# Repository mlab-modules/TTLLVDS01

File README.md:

<!--- PrjInfo ---> <!--- Please remove this line after manually editing --->
<!--- 00a56be08b96043df9e37d6aff7b6990 --->
<!--- Created:2019-02-18 14:57:49.031132: ---> 
<!--- Author:: ---> 
<!--- AuthorEmail:: ---> 
<!--- Tags:: ---> 
<!--- Ust:: ---> 
<!--- Label --->
<!--- ELabel ---> 
<!--- Name:TTLLVDS01A: --->
# TTLLVDS01A
<!--- LongName --->
## TTL to LVDS converter and vice versa
<!--- ELongName ---> 

<!--- Lead --->
TTLLVDS is TTL to LVDS and LVDS to TTL converter. Module can be used to connect a simple TTL signal to LVDS input. By changing the components, it can acts as LVDS to TTL convertor. To covert differencial LVDS signal to TTL output. Each module converts two signals. 
<!--- ELead ---> 

<!--- Description --->
The TTL signal is connected using a simple header. Differential LVDS signal is connected trought SATA connector and cable. Each sata connector contains two pairs of LVDS signals.

Module require a 3v3 powering. 
<!--- EDescription --->
<!--- Content --->
<!--- EContent --->

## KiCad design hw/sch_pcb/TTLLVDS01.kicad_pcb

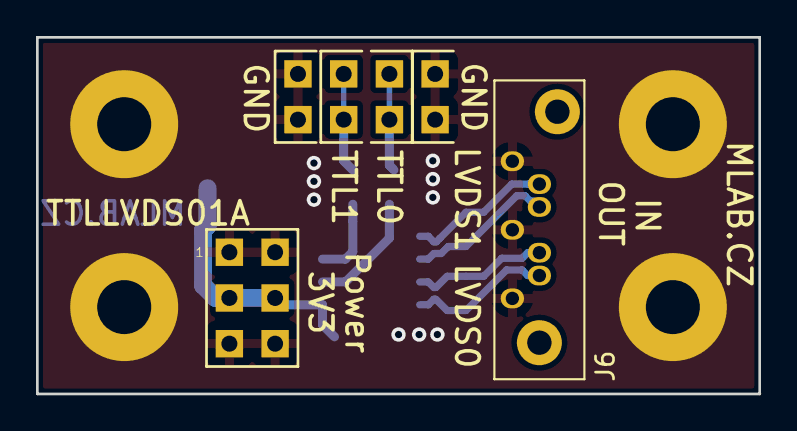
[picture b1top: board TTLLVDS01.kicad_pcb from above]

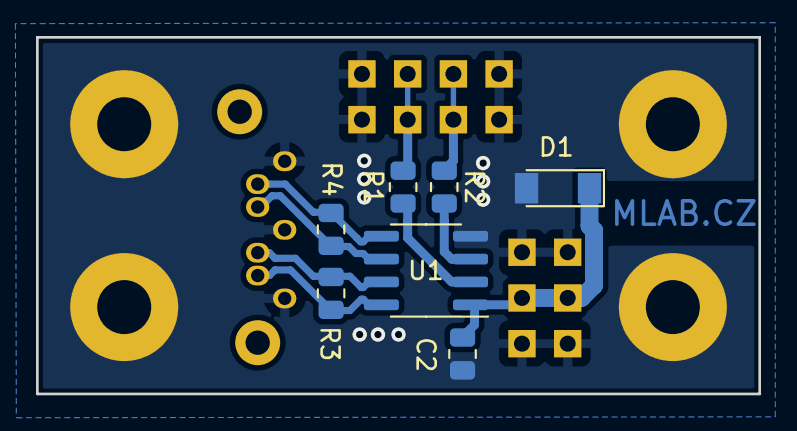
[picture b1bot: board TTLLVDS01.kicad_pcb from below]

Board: 2 copper layers, 40.1 x 19.8 mm, 17 parts (7 on the bottom side), 10 nets.

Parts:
C2: 100nF; R_0805_2012Metric
D1: BZV55C-3,6V; D_MiniMELF
J1: JUMP_3X2; Straight_2x03
J2, J3, J4, J5: HEADER_2x01_PARALLEL; Straight_2x01
J6: SATA7-67491-1030; SATA-7_THT_VERT_2
M1, M2, M3, M4: HOLE; MountingHole_3mm
R1, R2: 33R; R_0805_2012Metric
R3, R4: 100; R_0805_2012Metric
U1: SN65LVDS9638D; SOIC-8_3.9x4.9mm_P1.27mm

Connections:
/1+: J6.2, R3.1, U1.8 (1Y)
/1-: J6.3, R3.2, U1.7 (1Z)
/1A: J2.1, J2.2, R1.2
/2+: J6.5, R4.1, U1.6 (2Y)
/2-: J6.6, R4.2, U1.5 (2Z)
/2A: J4.1, J4.2, R2.2
GND: C2.2, D1.2 (A), J1.1 (2), J1.2, J1.5 (6), J1.6, J3.1, J3.2, J5.1, J5.2, J6.1, J6.4, J6.7, M1.1, M2.1, M3.1, M4.1, U1.4 (GND)
unnamed: R1.1, U1.2 (1A)
unnamed: R2.1, U1.3 (2A)
VCC: C2.1, D1.1 (K), J1.3 (4), J1.4, U1.1 (VCC)

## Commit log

2019-02-18 [MLABweb] Documentaion edits; TTLLVDS01A
2019-02-19 edit
2019-02-19 Edit PCB
2019-03-13 datasheet to SN65LVDS9638
2019-04-08 Rendering printable file.
2022-03-08 Update project to KiCAD 6.0. Update PCB silkscreen.
2022-04-04 Update documentation.
2022-04-04 Add github actions to module.
2022-04-04 Fix wrong path organisation.
2022-04-04 Fix title block path issue. Fix submodule versions.
2022-04-04 Update actions products
2022-04-04 exclude drc error
2022-04-05 add license
2022-04-06 automated commit; add github actions
2022-05-06 Zmena pouzder na nova KiCAD a poslední kontroly pred vyrobou
2022-05-25 Priprava podkladu pro vyrobu
2023-07-05 automated commit; rename source files to new naming convence
